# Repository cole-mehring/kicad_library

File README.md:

# kicad_library
My custom kicad library

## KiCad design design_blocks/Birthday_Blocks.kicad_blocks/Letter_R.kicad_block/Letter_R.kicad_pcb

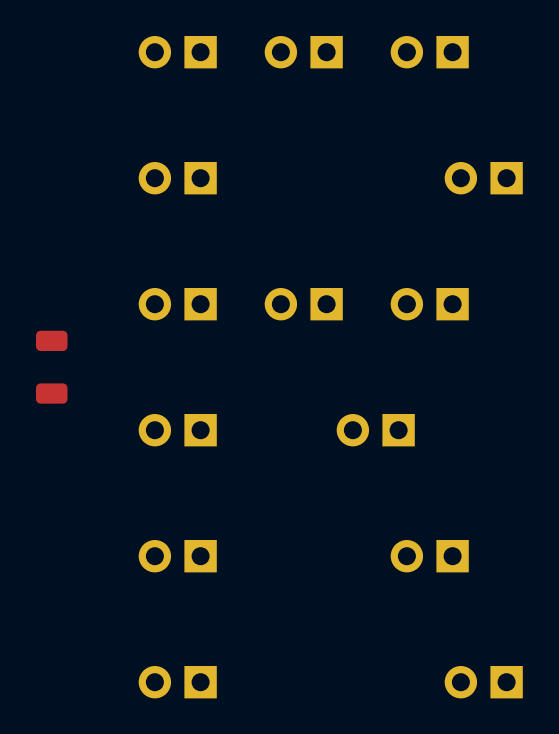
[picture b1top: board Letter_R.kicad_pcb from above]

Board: 2 copper layers, 15 parts (0 on the bottom side), 2 nets, no tracks yet.

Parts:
D1, D2, D3, D4, D5, D6, D7, D8, D9, D10, D11, D12, D13, D14: 151051VS04000; LED_D5.0mm_WE-WL-TMRC_AnodePin1
R1: RC1206FR-076R2L; R_1206_3216Metric

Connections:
/K: D1.2, D2.2, D3.2, D4.2, D5.2, D6.2, D7.2, D8.2, D9.2, D10.2, D11.2, D12.2, D13.2, D14.2
unnamed: D1.1, D2.1, D3.1, D4.1, D5.1, D6.1, D7.1, D8.1, D9.1, D10.1, D11.1, D12.1, D13.1, D14.1, R1.2
